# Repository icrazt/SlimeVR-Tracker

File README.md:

# SlimeVR-Tracker  CC Version

Crazt 的小体积 SlimeVR 硬件方案

## Components

主要器件选型：

| Main Component | Specification                    | Note                                                         |
| -------------- | -------------------------------- | ------------------------------------------------------------ |
| SoC Module     | ESP32-C3-MINI-1                  |                                                              |
| IMU            | BNO085                           | IMU Comparison [BNO085](https://docs.slimevr.dev/diy/imu-comparison.html#bno085) |
| Charging       | LGS4084HB6                       | 400 mA charging current                                      |
| Power Supply   | SY8088IAAC                       | step down DC/DC regulator，1A output current                 |
| Battery        | 1000mAh polymer lithium battery, | `35*25*10mm` (WxLxH) or 102535, Molex 1.25 2pin connector, 35mm lead length |

PCB 接口：

| Interfaces                   | Specification                          | Note                            |
| ---------------------------- | -------------------------------------- | ------------------------------- |
| USB                          | USB4105 - **Type C** USB 2.0 Connector | charging and firmware burning   |
| Sub-tracking interface (AUX) | JST_GH_SM05B                           | self-locking connector          |
| Pogo pin connector           | 2 pin  2.5mm pitch                     | reserve for future charging hub |
| UART pad                     | 4 pin 1.25mm pitch                     | *first time  firmware burning   |

补充说明：

1. 选用 ESP32-C3-MINI-1 小体积模组，搭载 RISC-V 32 位单核处理器，时钟频率高达 160 MHz。支持 [USB CDC  串口连接](https://www.espressif.com/sites/default/files/documentation/esp32-c3_technical_reference_manual_cn.pdf#usbserialjtag)，无需添加其他芯片进行 USB-串口转换。
2. 电源部分使用 SY8088IAAC 1A 同步降压调节器，相比低压降(*LDO*) 稳压器效率更高，在搭配 1000mAh 电池时实测至少可用10小时
3. 电池管理部分选用 LGS4084HB6 线性充电芯片，在 400mAh 充电时温度稳定，不会因芯片结温过高触发保护
4. 外壳：FDM 3D 打印外壳 + 亚克力顶部盖板，胶水粘合
5. 绑带：推荐搭配 25mm 硅胶防滑魔术贴绑带使用
6. Pogo pin 连接器：为待设计的充电坞预留的弹簧式探针接口，目前未使用

## About PCB Project

PCB 工程使用 KiCAD 7.0.7 版本设计，如需编辑建议使用最新版本。

部分元件引用自我的个人元件库 [icrazt/crazt-kicad-library: Personal kicad library](https://github.com/icrazt/crazt-kicad-library)，建议修改工程前添加。

## Firmware

使用原版固件修改引脚和相关配置即可使用，引脚定义如下

```c
  #define PIN_IMU_SDA 5
  #define PIN_IMU_SCL 4
  #define PIN_IMU_INT 6
  #define PIN_IMU_INT_2 7
  #define PIN_BATTERY_LEVEL 0
  #define LED_PIN 8
```

可以直接通过我 fork 仓库中的个人分支构建适用于该硬件的固件：

[icrazt/SlimeVR-Tracker-ESP at dev_crazt](https://github.com/icrazt/SlimeVR-Tracker-ESP/tree/dev_crazt)

## Gallery

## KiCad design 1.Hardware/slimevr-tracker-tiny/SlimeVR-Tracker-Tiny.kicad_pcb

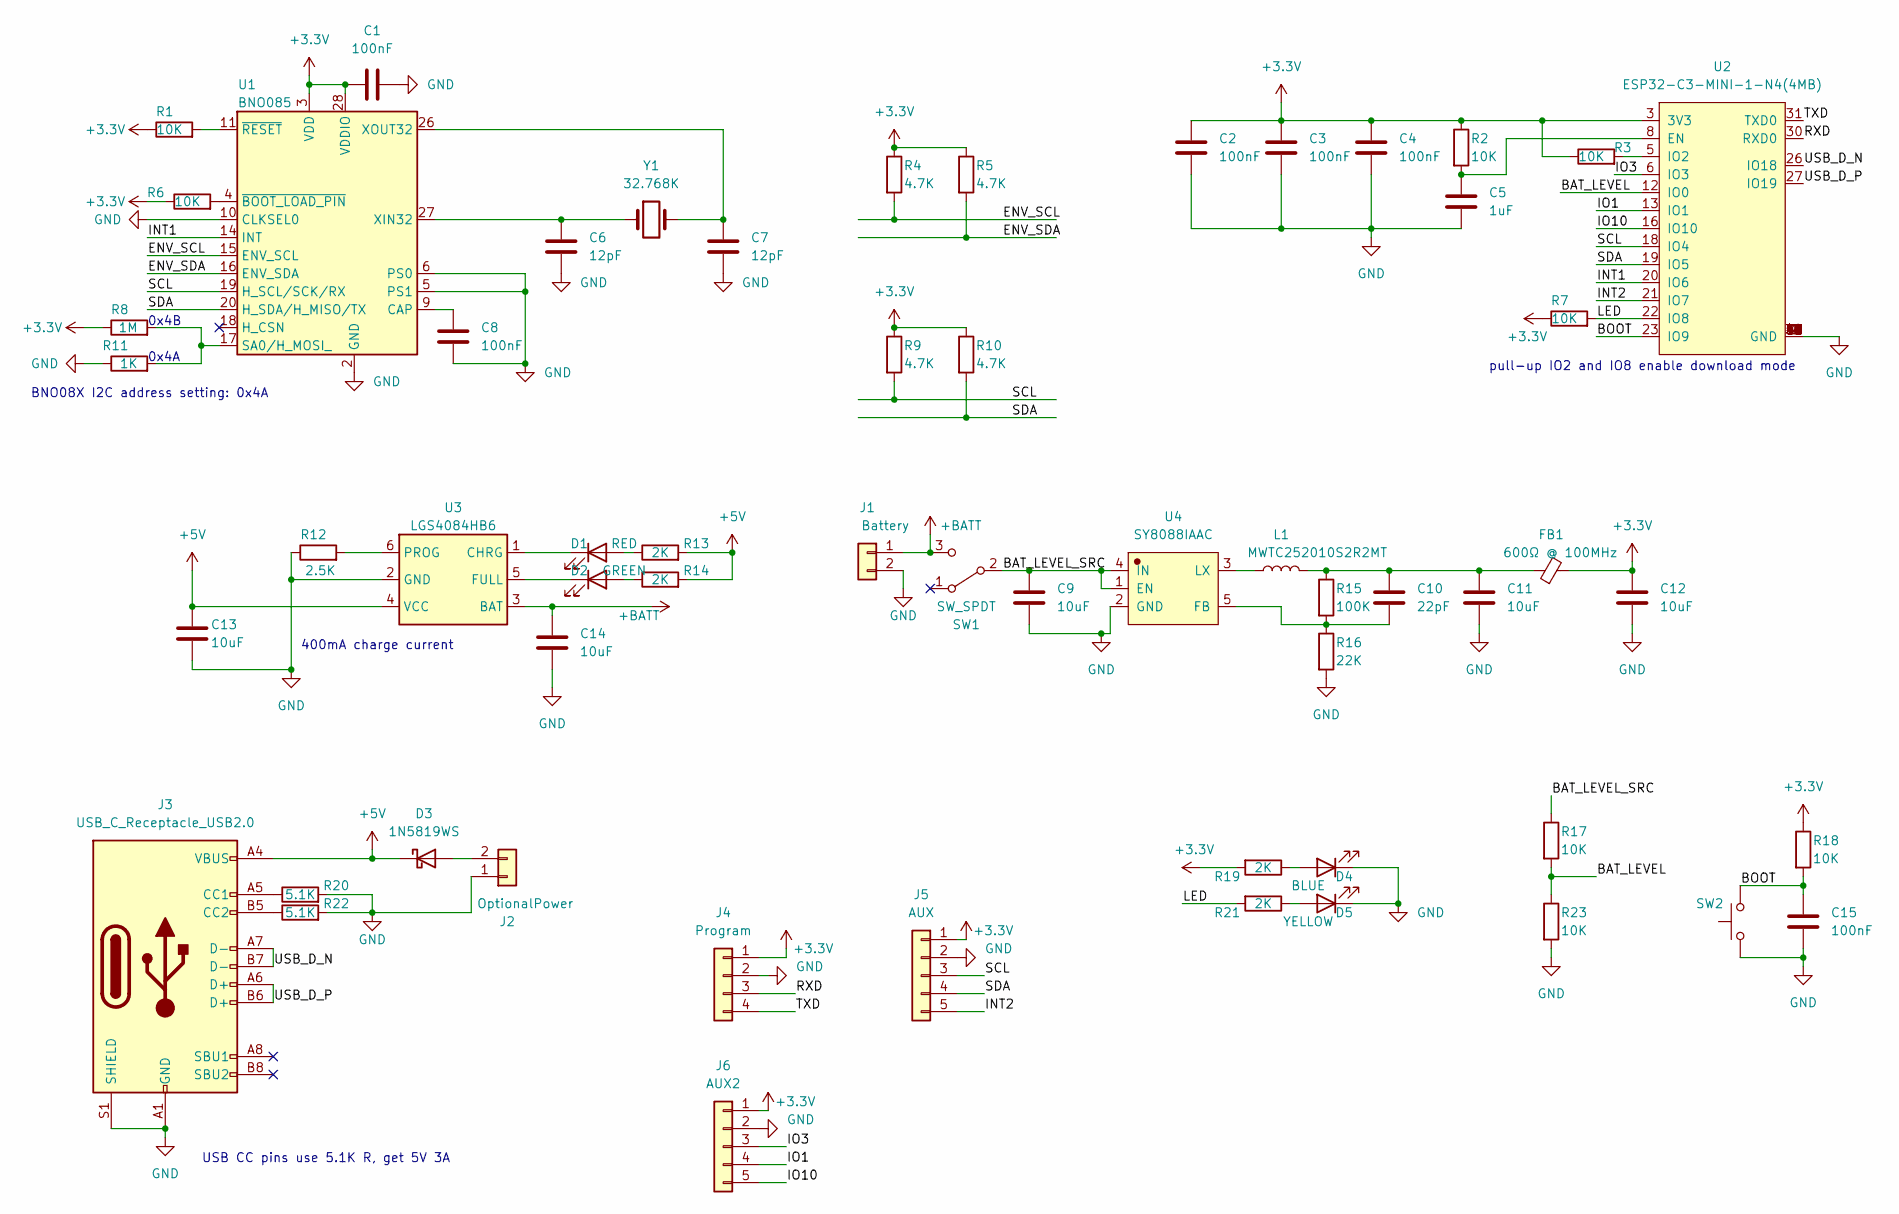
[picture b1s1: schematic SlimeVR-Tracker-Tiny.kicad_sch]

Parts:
C1, C2, C3, C4, C8, C15: 100nF; C_0402_1005Metric
C5: 1uF; C_0402_1005Metric
C6, C7: 12pF; C_0402_1005Metric
C9, C11, C12, C13, C14: 10uF; C_0402_1005Metric
C10: 22pF; C_0402_1005Metric
D1: RED; LED_0603_1608Metric
D2: GREEN; LED_0603_1608Metric
D3: 1N5819WS; D_SOD-323
D4: BLUE; LED_0603_1608Metric
D5: YELLOW; LED_0603_1608Metric
FB1: 600Ω @ 100MHz; L_0603_1608Metric
J1: Battery; Molex_PicoBlade_53261-0271_1x02-1MP_P1.25mm_Horizontal
J2: OptionalPower; YZ193115035T-02025-01
J3: USB_C_Receptacle_USB2.0; USB_C_Receptacle_GCT_USB4105-xx-A_16P_TopMnt_Horizontal
J4: Program; PinHeader_1x04_P1.27mm_Vertical
J5: AUX; JST_GH_SM05B-GHS-TB_1x05-1MP_P1.25mm_Horizontal
J6: AUX2; Pad_1x05_P1.27mm
L1: MWTC252010S2R2MT; L_Sunlord_SWPA252010S
R1, R2, R3, R6, R7, R17, R18, R23: 10K; R_0402_1005Metric
R4, R5, R9, R10: 4.7K; R_0402_1005Metric
R8: 1M; R_0402_1005Metric
R11: 1K; R_0402_1005Metric
R12: 2.5K; R_0402_1005Metric
R13, R14, R19, R21: 2K; R_0402_1005Metric
R15: 100K; R_0402_1005Metric
R16: 22K; R_0402_1005Metric
R20, R22: 5.1K; R_0402_1005Metric
SW1: SW_SPDT; SW_SPDT_PCM12
SW2: SW_Push; SW_Push_SPST_NO_Alps_SKRK
U1: BNO085; LGA-28_5.2x3.8mm_P0.5mm
U2: ESP32-C3-MINI-1-N4(4MB); WIFIM-SMD_ESP32-C3-MINI-1
U3: LGS4084HB6; SOT-23-6
U4: SY8088IAAC; SOT-23-5
Y1: 32.768K; Crystal_SMD_3215-2Pin_3.2x1.5mm

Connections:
+3.3V: C1.1, C2.1, C3.1, C4.1, C12.1, FB1.2, J4.1, J5.1, J6.1, R1.1, R2.1, R3.1, R4.1, R5.1, R6.1, R7.1, R8.1, R9.1, R10.1, R18.1, R19.2, U1.3 (VDD), U1.28 (VDDIO), U2.3 (3V3)
+5V: C13.1, D3.1 (K), J3.A4 (VBUS), J3.A9 (VBUS), J3.B4 (VBUS), J3.B9 (VBUS), R13.2, R14.2, U3.4 (VCC)
+BATT: C14.1, J1.1, SW1.3 (C), U3.3 (BAT)
/BAT_LEVEL: R17.2, R23.1, U2.12 (IO0)
/BAT_LEVEL_SRC: C9.1, R17.1, SW1.2 (B), U4.1 (EN), U4.4 (IN)
/BOOT: C15.1, R18.2, SW2.2, U2.23 (IO9)
/ENV_SCL: R4.2, U1.15 (ENV_SCL)
/ENV_SDA: R5.2, U1.16 (ENV_SDA)
/INT1: U1.14 (INT), U2.20 (IO6)
/INT2: J5.5, U2.21 (IO7)
/IO1: J6.4, U2.13 (IO1)
/IO3: J6.3, U2.6 (IO3)
/IO10: J6.5, U2.16 (IO10)
/LED: R7.2, R21.2, U2.22 (IO8)
/RXD: J4.3, U2.30 (RXD0)
/SCL: J5.3, R9.2, U1.19 (H_SCL/SCK/RX), U2.18 (IO4)
/SDA: J5.4, R10.2, U1.20 (H_SDA/H_MISO/TX), U2.19 (IO5)
/TXD: J4.4, U2.31 (TXD0)
/USB_D_N: J3.A7 (D-), J3.B7 (D-), U2.26 (IO18)
/USB_D_P: J3.A6 (D+), J3.B6 (D+), U2.27 (IO19)
GND: C1.2, C2.2, C3.2, C4.2, C5.2, C6.1, C7.1, C8.2, C9.2, C11.2, C12.2, C13.2, C14.2, C15.2, D4.1 (K), D5.1 (K), J1.2, J2.1, J3.A1 (GND), J3.A12 (GND), J3.B1 (GND), J3.B12 (GND), J3.S1 (SHIELD), J4.2, J5.2, J6.2, R11.1, R12.1, R16.2, R20.2, R22.2, R23.2, SW2.1, U1.2 (GND), U1.5 (PS1), U1.6 (PS0), U1.10 (CLKSEL0), U1.25 (GND), U2.1 (GND), U2.2 (GND), U2.11 (GND), U2.14 (GND), U2.36 (GND), U2.37 (GND), U2.38 (GND), U2.39 (GND), U2.40 (GND), U2.41 (GND), U2.42 (GND), U2.43 (GND), U2.44 (GND), U2.45 (GND), U2.46 (GND), U2.47 (GND), U2.48 (GND), U2.49 (GND), U2.50 (GND), U2.51 (GND), U2.52 (GND), U2.53 (GND), U3.2 (GND), U4.2 (GND)
unnamed: C10.1, C11.1, FB1.1, L1.2, R15.1
unnamed: D1.2 (A), R13.1
unnamed: D1.1 (K), U3.1 (CHRG)
unnamed: D2.2 (A), R14.1
unnamed: D2.1 (K), U3.5 (FULL)
unnamed: D3.2 (A), J2.2
unnamed: D4.2 (A), R19.1
unnamed: D5.2 (A), R21.1
unnamed: J3.A5 (CC1), R20.1
unnamed: J3.B5 (CC2), R22.1
unnamed: C8.1, U1.9 (CAP)
unnamed: R8.2, R11.2, U1.17 (SA0/H_MOSI_)
unnamed: C6.2, U1.27 (XIN32), Y1.1
unnamed: C7.2, U1.26 (XOUT32), Y1.2
unnamed: R6.2, U1.4 (~BOOT_LOAD_PIN)
unnamed: R1.2, U1.11 (~RESET)
unnamed: C5.1, R2.2, U2.8 (EN)
unnamed: R3.2, U2.5 (IO2)
unnamed: R12.2, U3.6 (PROG)
unnamed: C10.2, R15.2, R16.1, U4.5 (FB)
unnamed: L1.1, U4.3 (LX)

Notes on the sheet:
400mA charge current
BNO08X I2C address setting: 0x4A
pull-up IO2 and IO8 enable download mode
0x4A
USB CC pins use 5.1K R, get 5V 3A
0x4B

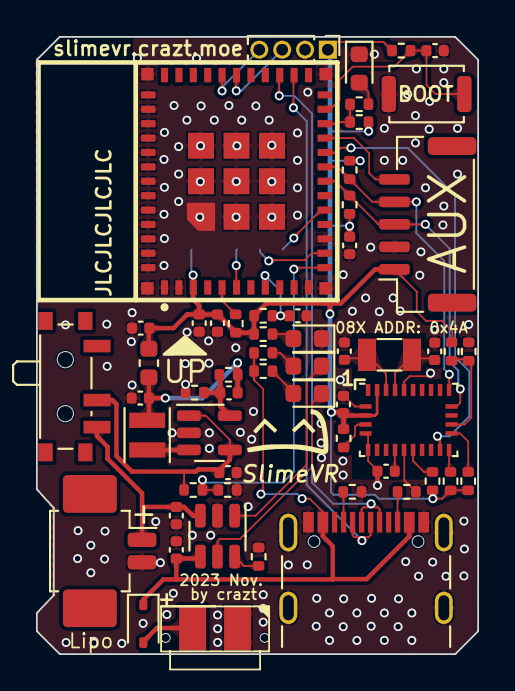
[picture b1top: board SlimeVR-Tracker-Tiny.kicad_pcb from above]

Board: 2 copper layers, 24.5 x 34.3 mm, 58 parts (1 on the bottom side), 42 nets.

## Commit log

2024-02-16 First public release with v0.3 hardware that has been validated in real-world use.
2024-03-15 [mechanic] revise tracker main box.
